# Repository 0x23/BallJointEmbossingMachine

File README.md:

# Ball Joint Embossing Machine

> **Work in Progress** — This project is not in a finished, well-documented, or ready-to-replicate state. It is shared as a starting point for anyone who wants to build upon it. Expect incomplete documentation, rough edges, and parts that may require adaptation.

## Overview

A motorized linear embossing machine designed to precisely press ball joints. It was designed to automate the production of balljoint linkages for the [Open-Micro-Manipulator](https://github.com/0x23/MicroManipulatorStepper). It uses a NEMA 17 stepper motor driving a leadscrew on an MGN9 linear rail, with closed-loop position feedback from an MT6835 magnetic encoder. The tool head position is controlled in real time by firmware running on an RP2040 microcontroller.

## Hardware

- **Microcontroller:** RP2040-ZERO / RP2350-ZERO
- **Motor:** NEMA 17 stepper (1.8°, 50 pole pairs)
- **Motor driver:** TB6612
- **Position sensor:** MT6835 magnetic encoder (SPI)
- **Linear guide:** MGN9 rail + carriage
- **Drive:** Leadscrew with 3 mm magnet pitch, 48/20 gear ratio

## Electronics

> **WARNING: The electronics must be powered by no more than 5 V. Supplying a higher voltage will risk damaging the USB port on your Computer.**

The custom controller board (`electronics/ControllerBoardSingle_v1/`) is designed around the RP2040-ZERO / RP2350-ZERO and the TB6612 dual motor driver. Open the project with KiCad 10 or later. There is alwas a physical button to start the embossing process - please look at the firmware for finding the correct pin.

## Firmware

The firmware is built with [PlatformIO](https://platformio.org/).

**Build & upload:**
```bash
cd firmware
pio run --target upload
```

**Linux note:** udev rules must be installed before the upload will work:
```bash
sudo curl -fsSL https://raw.githubusercontent.com/platformio/platformio-core/develop/platformio/assets/system/99-platformio-udev.rules \
  -o /etc/udev/rules.d/99-platformio-udev.rules
sudo service udev restart
# replug the device, then run pio run --target upload
```

## License

MIT — see [LICENSE](LICENSE) for the full text.

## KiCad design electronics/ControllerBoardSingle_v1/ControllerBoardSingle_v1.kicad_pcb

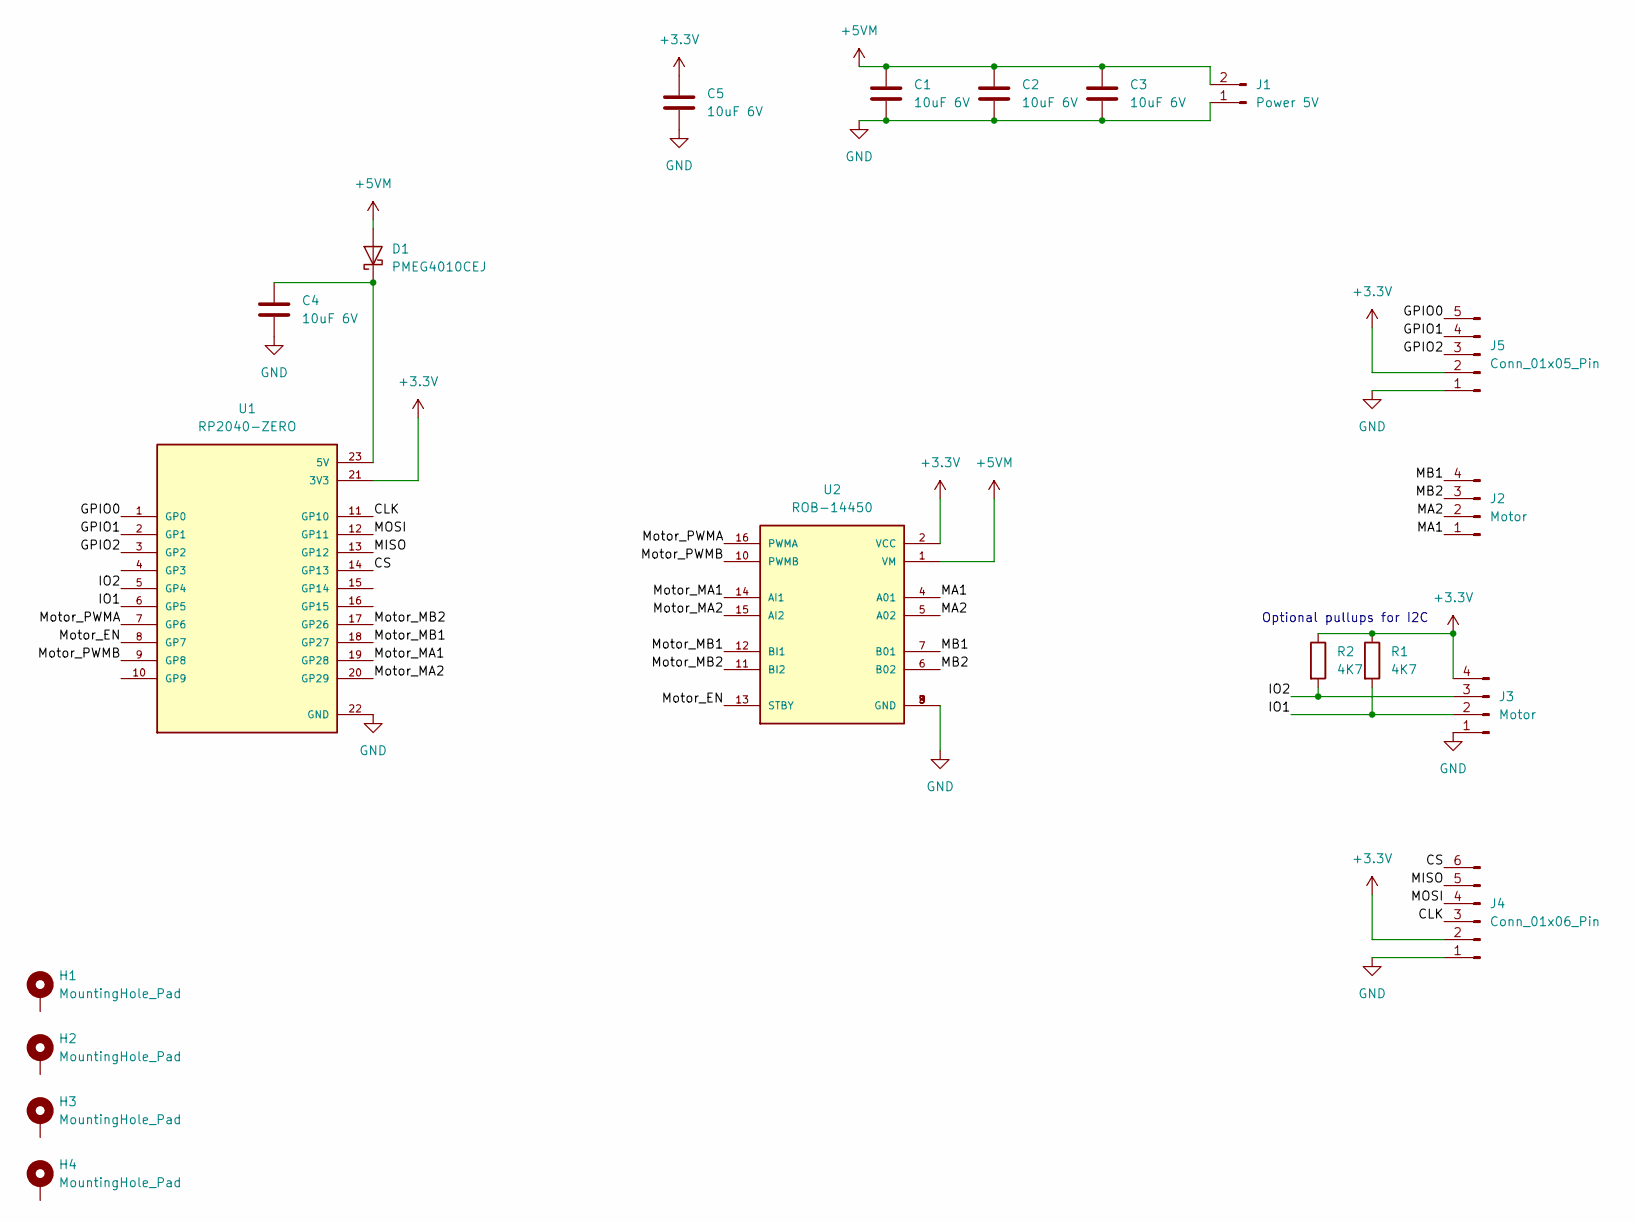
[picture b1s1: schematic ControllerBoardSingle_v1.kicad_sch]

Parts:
C1, C2, C3, C4, C5: 10uF 6V; C_0805_2012Metric_Pad1.18x1.45mm_HandSolder
D1: PMEG4010CEJ; D_SOD-123F
H1, H2, H3, H4: MountingHole_Pad; MountingHole_3.2mm_M3_ISO7380_Pad
J1: Power 5V; PinHeader_1x02_P2.54mm_Horizontal
J2, J3: Motor; JST_PH_B4B-PH-K_1x04_P2.00mm_Vertical
J4: Conn_01x06_Pin; JST_PH_B6B-PH-K_1x06_P2.00mm_Vertical
J5: Conn_01x05_Pin; PinSocket_1x05_P2.00mm_Vertical
R1, R2: 4K7; R_0603_1608Metric_Pad0.98x0.95mm_HandSolder
U1: RP2040-ZERO; MODULE_RP2040-ZERO; PARTREV NA
U2: ROB-14450; MODULE_ROB-14450; PARTREV 11-13-17

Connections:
+3.3V: C5.1, J3.4, J4.2, J5.2, R1.1, R2.1, U1.21 (3V3), U2.2 (VCC)
+5VM: C1.1, C2.1, C3.1, D1.2 (A), J1.2, U2.1 (VM)
/CLK: J4.3, U1.11 (GP10)
/CS: J4.6, U1.14 (GP13)
/GPIO0: J5.5, U1.1 (GP0)
/GPIO1: J5.4, U1.2 (GP1)
/GPIO2: J5.3, U1.3 (GP2)
/IO1: J3.2, R1.2, U1.6 (GP5)
/IO2: J3.3, R2.2, U1.5 (GP4)
/MA1: J2.1, U2.4 (A01)
/MA2: J2.2, U2.5 (A02)
/MB1: J2.4, U2.7 (B01)
/MB2: J2.3, U2.6 (B02)
/MISO: J4.5, U1.13 (GP12)
/MOSI: J4.4, U1.12 (GP11)
/Motor_EN: U1.8 (GP7), U2.13 (STBY)
/Motor_MA1: U1.19 (GP28), U2.14 (AI1)
/Motor_MA2: U1.20 (GP29), U2.15 (AI2)
/Motor_MB1: U1.18 (GP27), U2.12 (BI1)
/Motor_MB2: U1.17 (GP26), U2.11 (BI2)
/Motor_PWMA: U1.7 (GP6), U2.16 (PWMA)
/Motor_PWMB: U1.9 (GP8), U2.10 (PWMB)
GND: C1.2, C2.2, C3.2, C4.2, C5.2, J1.1, J3.1, J4.1, J5.1, U1.22 (GND), U2.3 (GND), U2.8 (GND), U2.9 (GND)
unnamed: C4.1, D1.1 (K), U1.23 (5V)

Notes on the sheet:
Optional pullups for I2C

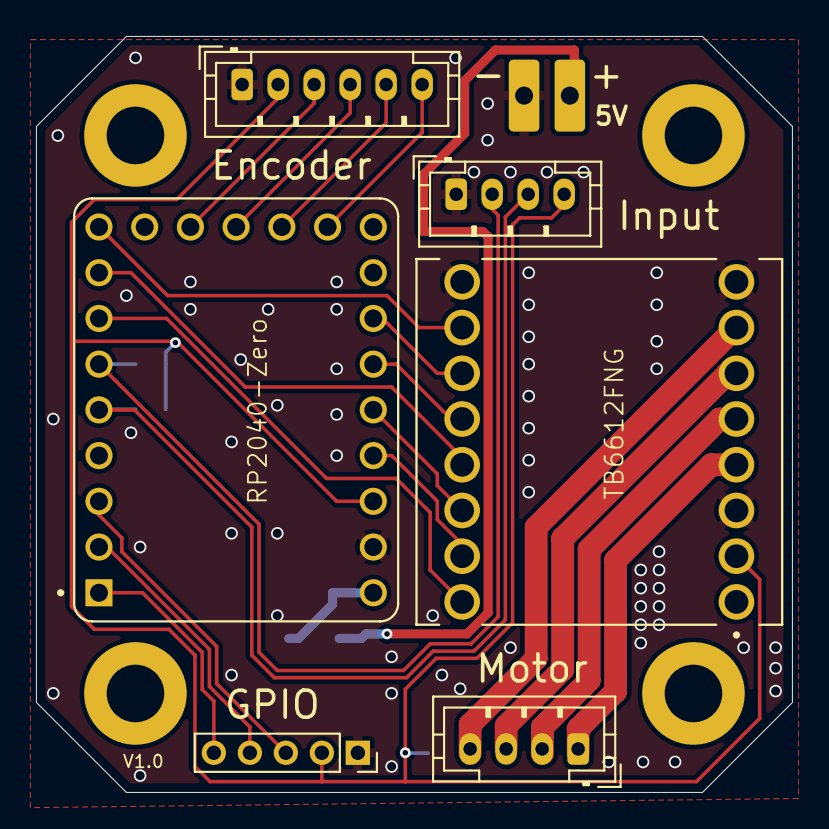
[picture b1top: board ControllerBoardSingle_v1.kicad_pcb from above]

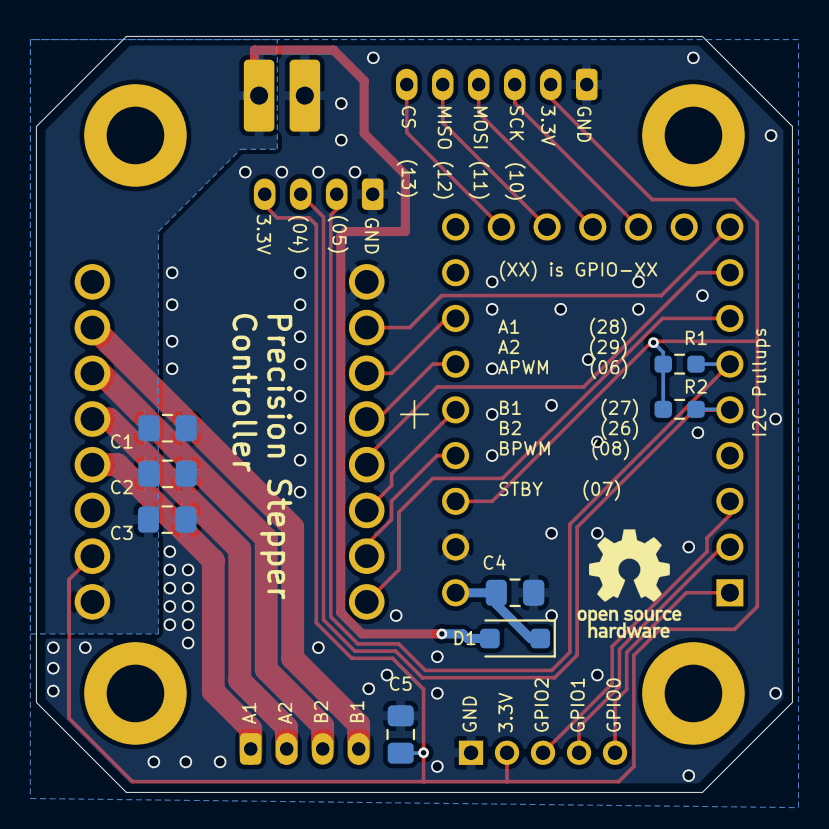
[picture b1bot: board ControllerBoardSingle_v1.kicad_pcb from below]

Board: 2 copper layers, 42.0 x 42.0 mm, 19 parts (8 on the bottom side), 24 nets.

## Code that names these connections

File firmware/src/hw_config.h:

// motor pole pair count
//  * 100 for 0.9deg stepper motors
//  * 50  for 1.8deg stepper motors
#define MOTOR_POLE_PAIRS 50
#define ROTATIONS_PER_MM (48.0f/20.0f/1.0f)
#define ENCODER_MAGNET_PITCH 3.0f

// Single Axis Board
#define PIN_BUILTIN_LED 16
#define PIN_USER_BUTTON PIN_GPIO_2

#define PIN_GPIO_0 0
#define PIN_GPIO_1 1
#define PIN_GPIO_2 2

#define PIN_M_PWM_A_POS  28
#define PIN_M_PWM_A_NEG  29
#define PIN_M_PWM_B_POS  27
#define PIN_M_PWM_B_NEG  26

#define PIN_MOTOR_EN      7
#define PIN_MOTOR_PWMA    6
#define PIN_MOTOR_PWMB    8

// note single axis board uses spi1
#define ENCODER_SPI spi1
#define PIN_ENCODER_CS 13
#define PIN_ENCODER_SCK 10
#define PIN_ENCODER_MISO 12
#define PIN_ENCODER_MOSI 11
